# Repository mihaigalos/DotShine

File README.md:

Fuse Settings:

Ext, Hi, Lo : FE DA EF
Lock: EF

During operation at low voltages (i.e. < 3V3), the clock needs to be scaled back to i.e. 2Mhz.
Do this in software, *not* in the fusebits. This is to continue allowing the USB bootloader.

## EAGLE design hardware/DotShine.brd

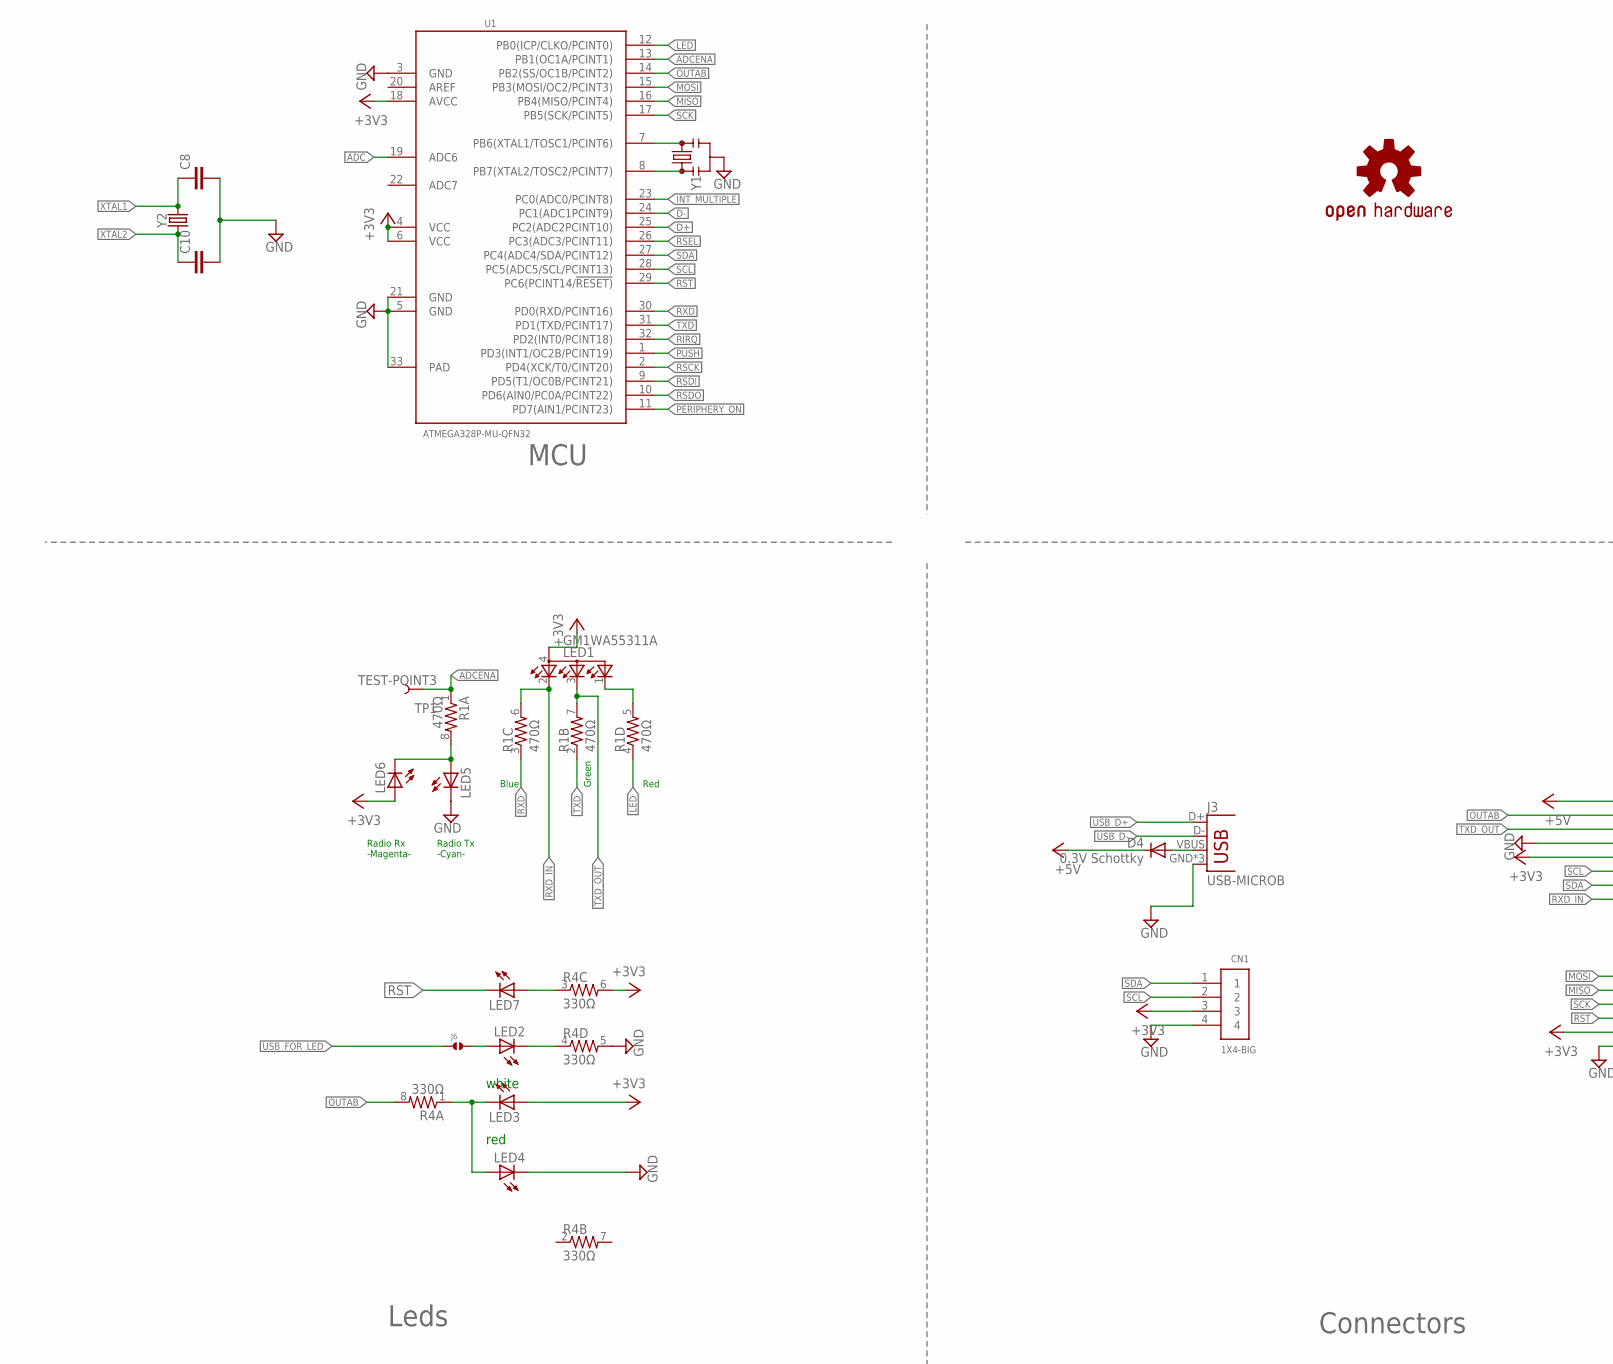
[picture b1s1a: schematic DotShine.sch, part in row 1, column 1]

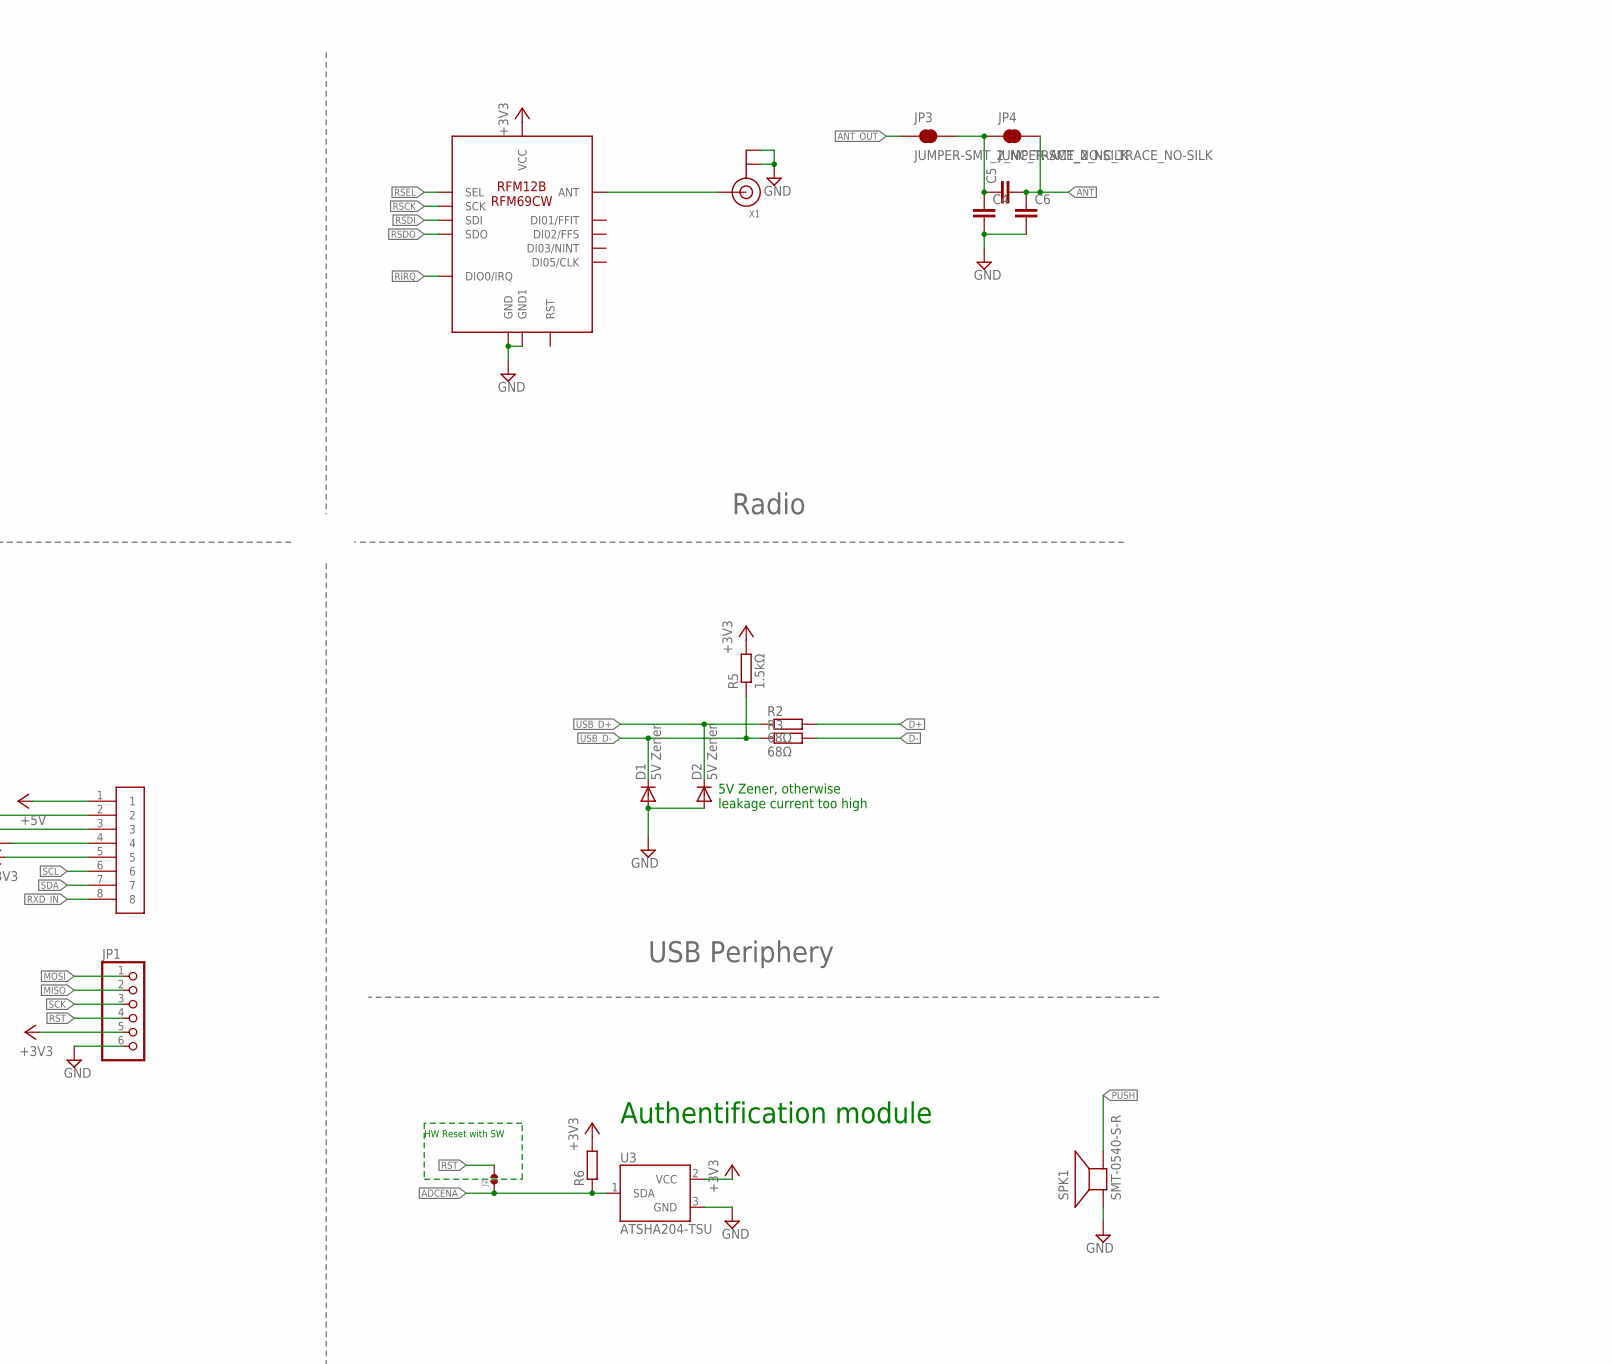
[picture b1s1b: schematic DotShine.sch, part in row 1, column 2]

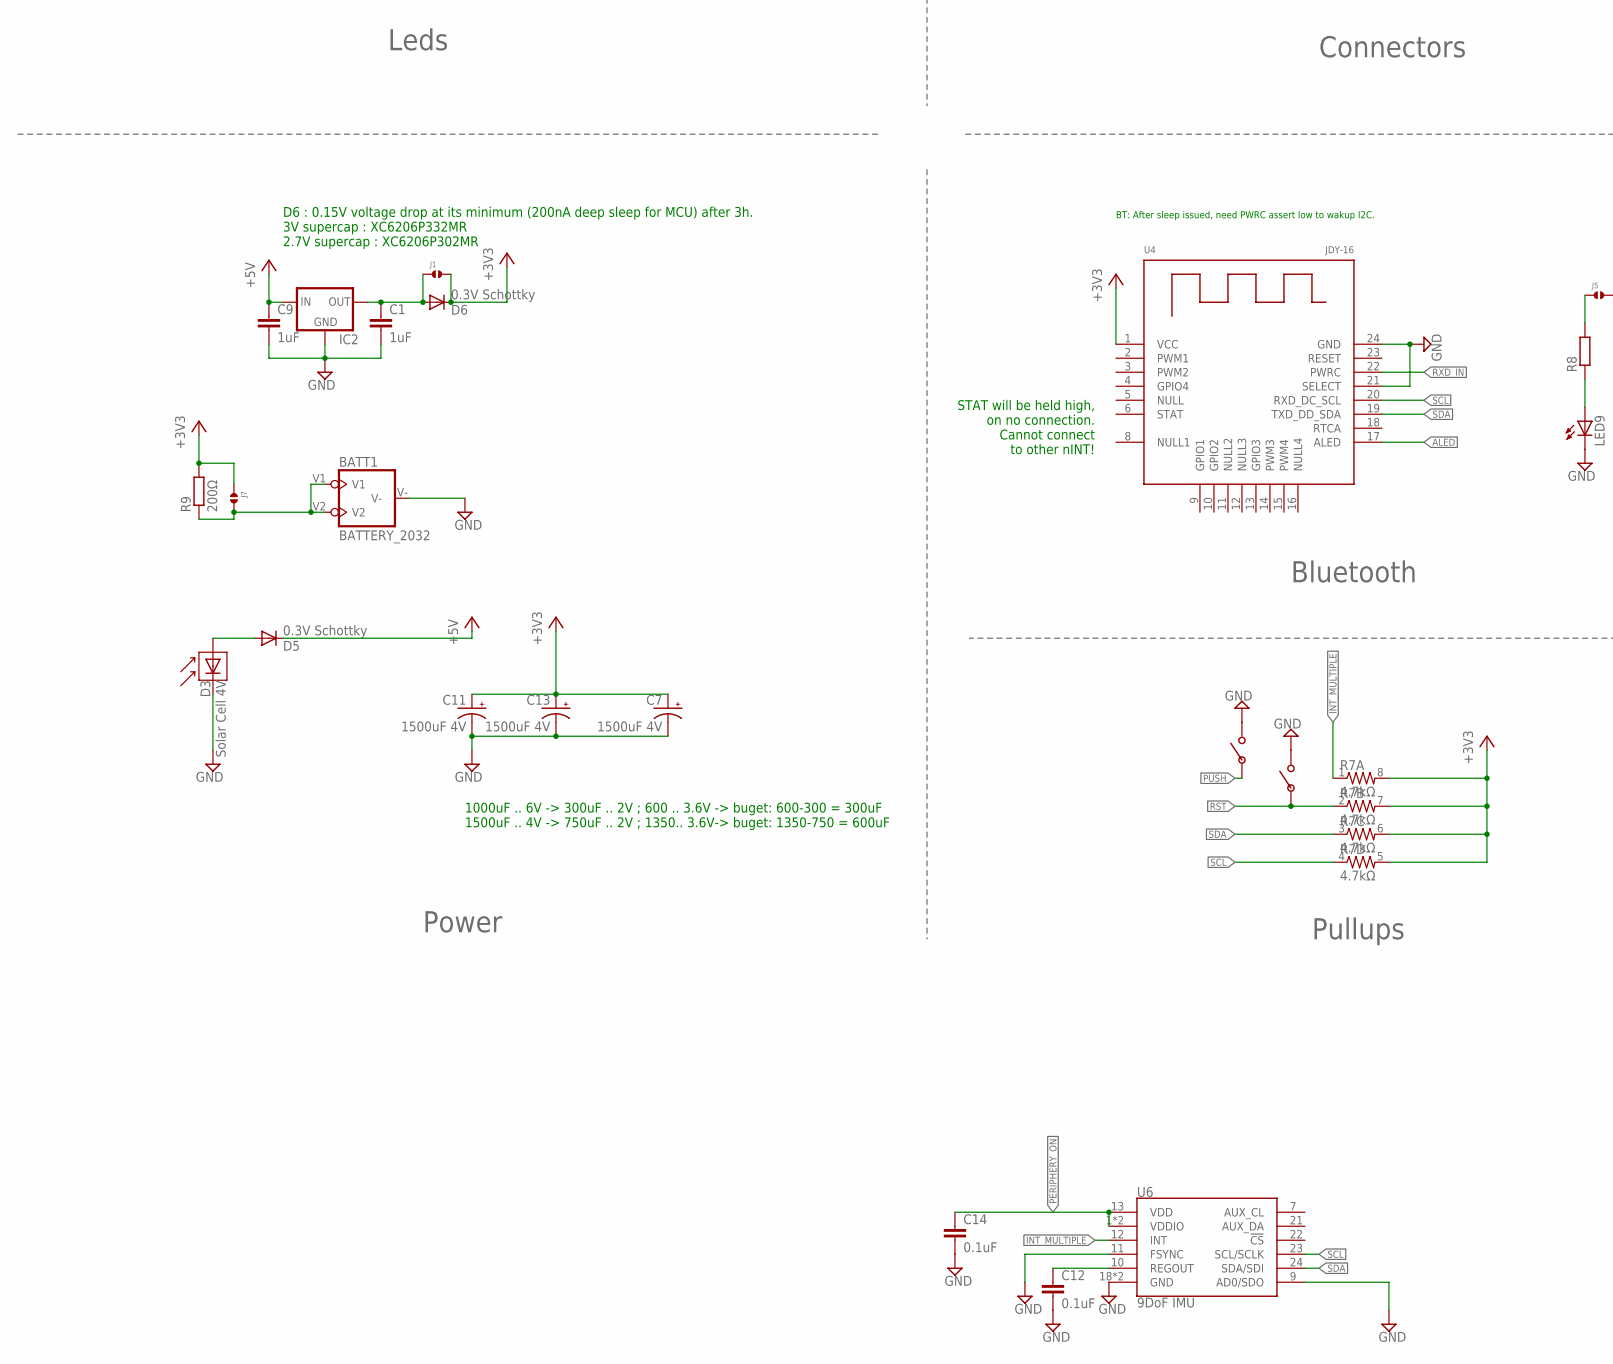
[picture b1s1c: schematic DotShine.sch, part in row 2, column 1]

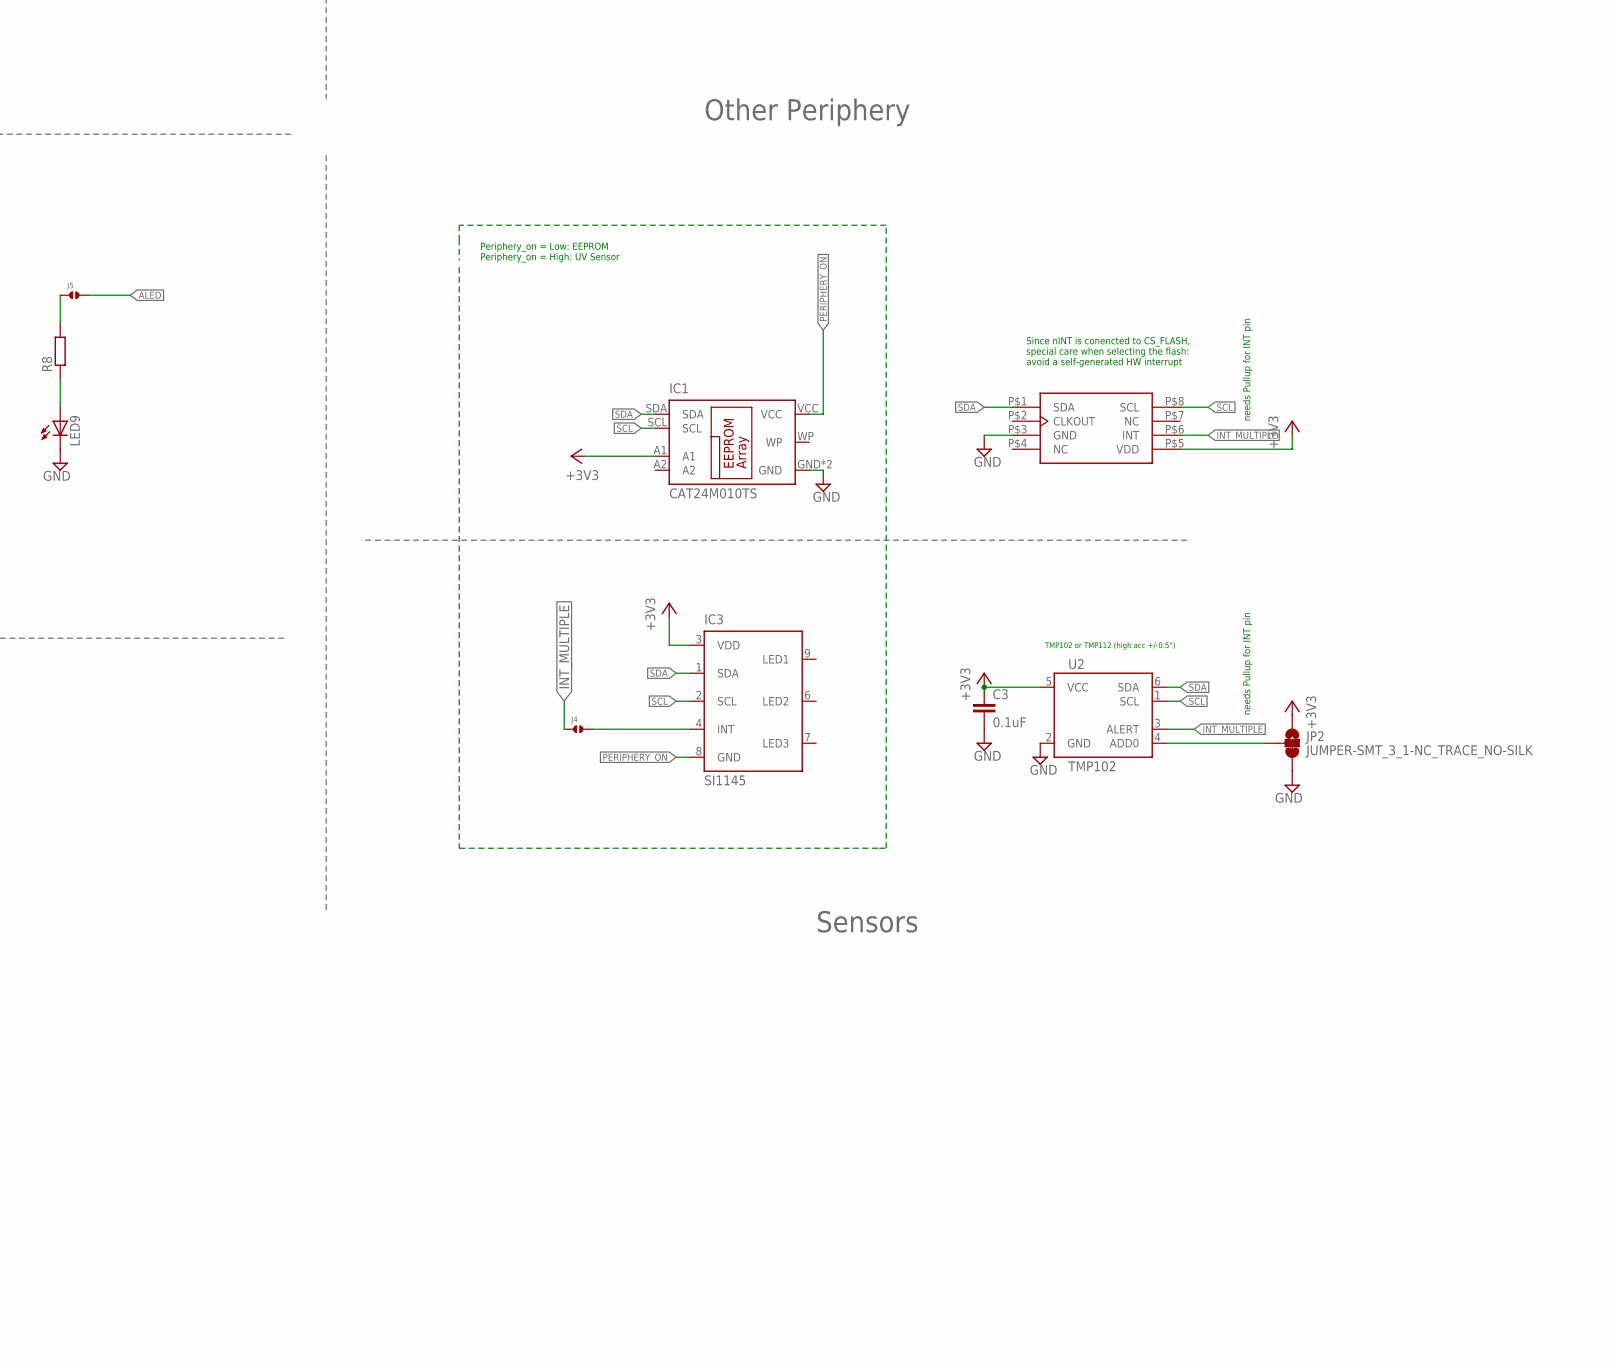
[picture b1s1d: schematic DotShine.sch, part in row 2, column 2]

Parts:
BATT1: BATTERY_2032; BATT2032
C1, C9: 1uF; C0603
C3, C12, C14: 0.1uF; C0603
C4, C5, C6: C-EUC0603; C0603
C7, C11, C13: 1500uF 4V; CT7343
C8, C10: C-EUC0402; C0402
CN1: 1X4-BIG; 1X04-BIG
D1, D2: 5V Zener; SOD523
D3: Solar Cell 4V; SOLARBIT-12X1
D4, D5, D6: 0.3V Schottky; SOD523
IC1: CAT24M010TS; TSSOP8
IC2: MCP1700TT; SOT-23
IC3: SI1145; QFN-10
J1, J2, J4, J5, J6, J7: SOLDERJUMPER.2.MED; 2.MED
J3: USB-MICROB
JP1: PINHD-1X6; 1X06
JP2: JUMPER-SMT_3_1-NC_TRACE_NO-SILK; SMT-JUMPER_3_1-NC_TRACE_NO-SILK
JP3, JP4: JUMPER-SMT_2_NC_TRACE_NO-SILK; SMT-JUMPER_2_NC_TRACE_NO-SILK
LED1: GM1WA55311A
LED2, LED3, LED4, LED5, LED6, LED7, LED9: LED0603; LED-0603
LOGO1: OSHW-LOGOS; OSHW-LOGO-S
R1: 470Ω; 0603-ARV
R2, R3: 68Ω; R0603
R4: 330Ω; 0603-ARV
R5: 1.5kΩ; R0603
R6, R8: R-EU_R0603; R0603
R7: 4.7kΩ; 0603-ARV
R9: 200Ω; R0603
SPK1: SMT-0540-S-R
TP1: TEST-POINT3; PAD.03X.03
U1: ATMEGA328P-MU-QFN32; QFN32G-0.5-5X5MM
U2: TMP102; SOT563
U3: ATSHA204-TSU; SOT23-3
U4: JDY-16
U6: 9DoF IMU; QFN24-3X3
U$1: RFM12B/69CW
U$2, U$3: PUSHBUTTON_4X2.5
U$4: JST-8; S4B-ZR
X1: ANTENNA_U.FL; U.FL
X2: MC-RTC-RV-4162-C7-I2C; MC-RTC-C7
Y1: RESONATORSMD-3.2X1.3; RESONATOR-SMD-3.2X1.3
Y2: CRYSTALSMD-3.2X1.5; CRYSTAL-SMD-3.2X1.5MM

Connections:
+3V3: C3.1, C7.+, C11.+, C13.+, CN1.3, D6.C, IC1.A1, IC3.3 (VDD), J1.2, J7.1, JP1.5, JP2.1, LED1.4 (A), LED3.A, LED6.A, R4.6 (2), R5.2, R6.2, R7.5 (2), R7.6 (2), R7.7 (2), R7.8 (2), R9.2, U1.4 (VCC), U1.6 (VCC), U1.18 (AVCC), U2.5 (VCC), U3.2 (VCC), U4.1 (VCC), U$1.VDD (VCC), U$4.5, X2.P$5 (VDD)
+5V: C9.1, D4.C, D5.C, IC2.3 (IN), U$4.1
ADC: U1.19 (ADC6)
ADCENA: J2.1, R1.1, R6.1, TP1.P$1, U1.13 (PB1(OC1A/PCINT1)), U3.1 (SDA)
ALED: J5.2, U4.17 (ALED)
ANT: C5.2, C6.1, JP4.2
ANT_OUT: JP3.1, U$1.ANT, X1.3 (SIGNAL)
D+: R2.2, U1.25 (PC2(ADC2PCINT10))
D-: R3.2, U1.24 (PC1(ADC1PCINT9))
GND: BATT1.V-, C1.2, C3.2, C4.2, C6.2, C7.-, C8.2, C9.2, C10.2, C11.-, C12.2, C13.-, C14.2, CN1.4, D1.A, D2.A, D3.- (C), IC1.GND, IC1.NC (GND), IC2.1 (GND), J3.GND, J3.MT1 (GND), J3.MT2 (GND), JP1.6, JP2.3, LED4.C, LED5.C, LED9.C, R4.5 (2), SPK1.- (+), U1.3 (GND), U1.5 (GND), U1.21 (GND), U1.33 (PAD), U2.2 (GND), U3.3 (GND), U4.21 (SELECT), U4.24 (GND), U6.9 (AD0/SDO), U6.11 (FSYNC), U6.18 (GND), U6.20 (GND), U$1.GND, U$1.GND1, U$2.P$2, U$3.P$2, U$4.4, X1.1 (GND), X1.2 (GND), X2.P$3 (GND), Y1.2
INT_MULTIPLE: J4.1, R7.1, U1.23 (PC0(ADC0/PCINT8)), U2.3 (ALERT), U6.12 (INT), X2.P$6 (INT)
LED: R1.4 (1), U1.12 (PB0(ICP/CLKO/PCINT0))
MISO: JP1.2, U1.16 (PB4(MISO/PCINT4))
MOSI: JP1.1, U1.15 (PB3(MOSI/OC2/PCINT3))
unnamed: J5.1, R8.2
unnamed: C4.1, C5.1, JP3.2, JP4.1
unnamed: LED9.A, R8.1
unnamed: U1.7 (PB6(XTAL1/TOSC1/PCINT6)), Y1.3
unnamed: LED2.C, R4.4 (1)
unnamed: U1.8 (PB7(XTAL2/TOSC2/PCINT7)), Y1.1
unnamed: LED3.C, LED4.A, R4.1
unnamed: LED7.A, R4.3 (1)
unnamed: JP2.2, U2.4 (ADD0)
unnamed: LED5.A, LED6.C, R1.8 (2)
unnamed: LED1.1 (CGREEN), R1.5 (2)
unnamed: C1.1, D6.A, IC2.2 (OUT), J1.1
unnamed: IC3.4 (INT), J4.2
unnamed: J6.2, LED2.A
unnamed: BATT1.V1, BATT1.V2, J7.2, R9.1
unnamed: C12.1, U6.10 (REGOUT)
OUTAB: R4.8 (2), U1.14 (PB2(SS/OC1B/PCINT2)), U$4.2
PERIPHERY_ON: C14.1, IC1.VCC, IC3.8 (GND), U1.11 (PD7(AIN1/PCINT23)), U6.1 (VDDIO), U6.8 (VDDIO), U6.13 (VDD)
PUSH: SPK1.+ (-), U1.1 (PD3(INT1/OC2B/PCINT19)), U$3.P$1
RIRQ: U1.32 (PD2(INT0/PCINT18)), U$1.IRQ (DIO0/IRQ)
RSCK: U1.2 (PD4(XCK/T0/CINT20)), U$1.SCK
RSDI: U1.9 (PD5(T1/OC0B/PCINT21)), U$1.SDI
RSDO: U1.10 (PD6(AIN0/PC0A/PCINT22)), U$1.SDO
RSEL: U1.26 (PC3(ADC3/PCINT11)), U$1.SEL
RST: J2.2, JP1.4, LED7.C, R7.2 (1), U1.29 (PC6(PCINT14/!RESET)), U$2.P$1
RXD: R1.3 (1), U1.30 (PD0(RXD/PCINT16))
RXD_IN: LED1.2 (CRED), R1.6 (2), U4.22 (PWRC), U$4.8
SCK: JP1.3, U1.17 (PB5(SCK/PCINT5))
SCL: CN1.2, IC1.SCL, IC3.2 (SCL), R7.4 (1), U1.28 (PC5(ADC5/SCL/PCINT13)), U2.1 (SCL), U4.20 (RXD_DC_SCL), U6.23 (SCL/SCLK), U$4.6, X2.P$8 (SCL)
SDA: CN1.1, IC1.SDA, IC3.1 (SDA), R7.3 (1), U1.27 (PC4(ADC4/SDA/PCINT12)), U2.6 (SDA), U4.19 (TXD_DD_SDA), U6.24 (SDA/SDI), U$4.7, X2.P$1 (SDA)
SOLAR_OUT: D3.+ (A), D5.A
TXD: R1.2 (1), U1.31 (PD1(TXD/PCINT17))
TXD_OUT: LED1.3 (CBLUE), R1.7 (2), U$4.3
USB_D+: D2.C, J3.D+, R2.1
USB_D-: D1.C, J3.D-, R3.1, R5.1
USB_FOR_LED: D4.A, J3.VBUS, J6.1
XTAL1: C8.1, Y2.P$2 (2)
XTAL2: C10.1, Y2.P$1 (1)

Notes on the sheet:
MCU
Radio
Blue
Green
Red
TMP102 or TMP112 (high acc +/-0.5°)
Authentification module
white
red
Since nINT is conencted to CS_FLASH, special care when selecting the flash: avoid a self-generated HW interrupt
needs Pullup for INT pin
Radio Rx -Magenta-
Radio Tx -Cyan-
1000uF .. 6V -> 300uF .. 2V ; 600 .. 3.6V -> buget: 600-300 = 300uF 1500uF .. 4V -> 750uF .. 2V ; 1350.. 3.6V-> buget: 1350-750 = 600uF
D6 : 0.15V voltage drop at its minimum (200nA deep sleep for MCU) after 3h. 3V supercap : XC6206P332MR 2.7V supercap : XC6206P302MR
5V Zener, otherwise leakage current too high
HW Reset with SW
BT: After sleep issued, need PWRC assert low to wakup I2C.
Periphery_on = Low: EEPROM Periphery_on = High: UV Sensor
Leds
Connectors
USB Periphery
Other Periphery
Power
Bluetooth
Pullups
Sensors
STAT will be held high, on no connection. Cannot connect to other nINT!

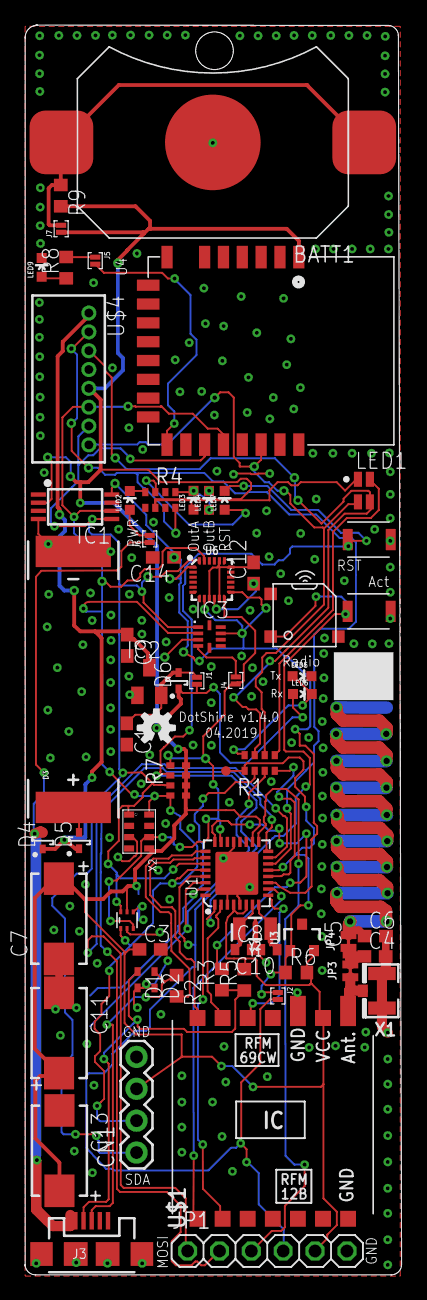
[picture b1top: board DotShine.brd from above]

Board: 2 copper layers, 30.0 x 99.6 mm, 68 parts (1 on the bottom side), 51 nets.

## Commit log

2018-06-29 Initial fork of hwrdware/ from DotPhat
2018-07-01 Beta: initial arrange of solar
2018-07-01 Reroute signals after repositioning
2018-07-02 Add TP for TRx leds
2018-07-02 Reposition components to accomodate possible LoRA RF
2018-07-02 Add FSK/LoRA silkscreen
2018-07-02 Add SJ for bypass threshold VCC, polarity markers
2018-07-02 Move SDA & GND silkscreen left
2018-07-07 Move caps from parallel to series
2018-07-07 Irrelevant since will be reverted
2018-07-07 Revert "Irrelevant since will be reverted"
    This reverts commit e891d672a37a9ace9540b21aee4dc257b77b94d6.
2018-07-07 Revert "Move caps from parallel to series"
    This reverts commit e29ebe1b9370ccceb9c5010c93145ac8bd52b422.
2018-07-13 Reposition logos
2018-07-14 Add .gitignore and .gitattributes
2018-07-14 Add 3rd solar cap
2018-07-14 Add capacity buget calculation
2018-07-14 Add mount hole
2018-07-14 Reposition Radio logo
2018-07-14 Correct diameter of fixation hole
2018-07-14 Refactor project name
2018-07-15 Increase space for radio Id
2018-07-20 Add schottky@LDO for solar powered operation
2018-08-03 Add support for IXYS SLMD121H9L solar cell 45mA@4.5V
2018-08-03 Account for panel of 62mm instead of 61mm
2018-08-04 Add tip to solar + pad for easy soldering
2018-08-04 Improve + pad
2018-08-04 Account for datasheet irregularities: len 61 or 62mm
2018-08-04 Remove soldermask @ solar gnd
2018-08-04 move i2c eeprom connections further down
2018-08-04 Add logo with correct pointer to DotShine
2018-08-04 Adjust bstop around +
2018-08-04 Add second zener if using large solar panel
2018-08-04 Add second strong zener if using large solar panel
2018-08-04 Correct unrouted traces
2018-08-04 Connect + of solar together, share Schottky
2018-08-10 On Led -> USB, now at 5V. Only on when usb present
2018-08-12 Add readme
2018-08-12 Rem superfluous Zener for solar, out it to LDO
2018-08-14 Separate USB Led from solar
2018-08-14 Move leftmost schottky left, overlap with stencil
2018-08-14 Realign leftmost schottky
2018-08-14 Add Schottky simbol to leftmost diode
2018-08-15 Improve usb power lines width
2018-08-19 Remove IXYS SLMD121H9L solar cell 45mA@4.5V, use small cell and i2c micro crystal
2018-08-19 Add RST led
2018-08-20 Add OG tag
2018-08-22 Invert cap, improve GND
2018-09-19 Refactor Caps from 5V to 3.3V, update version
2018-09-19 Add SJ for ADCENA and RST -> HW reset through SW
2018-09-20 Increase tracewidth near LDO
2018-09-20 Remove superfluous text
2018-09-20 Improve tracewidth near LDO
2018-09-21 Sync
2018-09-27 Add UV Sensor INT to cabled OR
2018-09-27 UV power controlled from MCU (no sleep), TXD to JST
2018-10-07 Update LDO description
2018-10-07 Initial version with BLE using JDY-16
2018-10-10 Initial bluetooth integration
2018-10-11 Add and flip JST8, add BLE logo
2018-10-16 Flip BT logo
2018-10-29 Flip bluetooth logo
2018-10-29 Revert "Flip bluetooth logo"
    This reverts commit 86c453a6030c35620ff411ae46af383bfef934ec.
2018-10-29 Mirror bluetooth logo to tBottom
2018-10-31 Add PWRC connection for BT, needed to assert low to reenable I2C
2018-11-01 Connect BT Stat to INT_MULTIPLE, SJ on ALED
2018-11-01 Reduce warnings
2018-11-02 Increase version
2018-11-03 SJ on PWR led
2018-11-27 Connect E2PROM A1 to 3V3, avoid collision with BLE
2018-11-27 Fix board schematic inconsistency
2018-11-27 Remove BLE RGB
2018-11-30 Update Ext fuse for 1.8V brown-out
2018-12-03 Improve GND
2018-12-03 I2C EEPROM Vdd controlled from MCU pin
2018-12-03 Improve naming
2018-12-03 Add reminder to measure minimize E2PROM current from MCU pin
2018-12-06 Add coincell
2018-12-07 Approve superfluous
2018-12-09 Tristate Periphery_On
2018-12-09 Restructure schematic in groups
2018-12-09 Improve restructuring
2018-12-11 Add second solar cell, consolidate GND
2018-12-11 Realign vertical drills
2018-12-11 Add supercap logo
2018-12-11 Remove Supercap logo
2018-12-11 Reposition PWR logo
2018-12-11 Reposition GND via in center of CR2032
2018-12-11 Reposition FSK/LoRA logos
2018-12-15 Add current limiter for coincell
2018-12-17 Add value for current limit for coincell
2018-12-20 Add 9DoF MPU9250, increase version
2019-01-20 Add missing 3V3 for OutA, RGB
2019-03-06 Add pullup to INT_MULTIPLE
2019-03-06 Optimize to 99mm for cost
2019-03-06 Increase version, optimize GND
2019-03-06 Optimize GND
2019-03-06 Approve irrelevant warnings

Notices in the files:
parts and their libraries:
SparkFun: Licensing: CC v3.0 Share-Alike You are welcome to use this library for commercial purposes.
SparkFun-Clocks: Licensing: Creative Commons ShareAlike 4.0 International - https://creativecommons.org/licenses/by-sa/4.0
